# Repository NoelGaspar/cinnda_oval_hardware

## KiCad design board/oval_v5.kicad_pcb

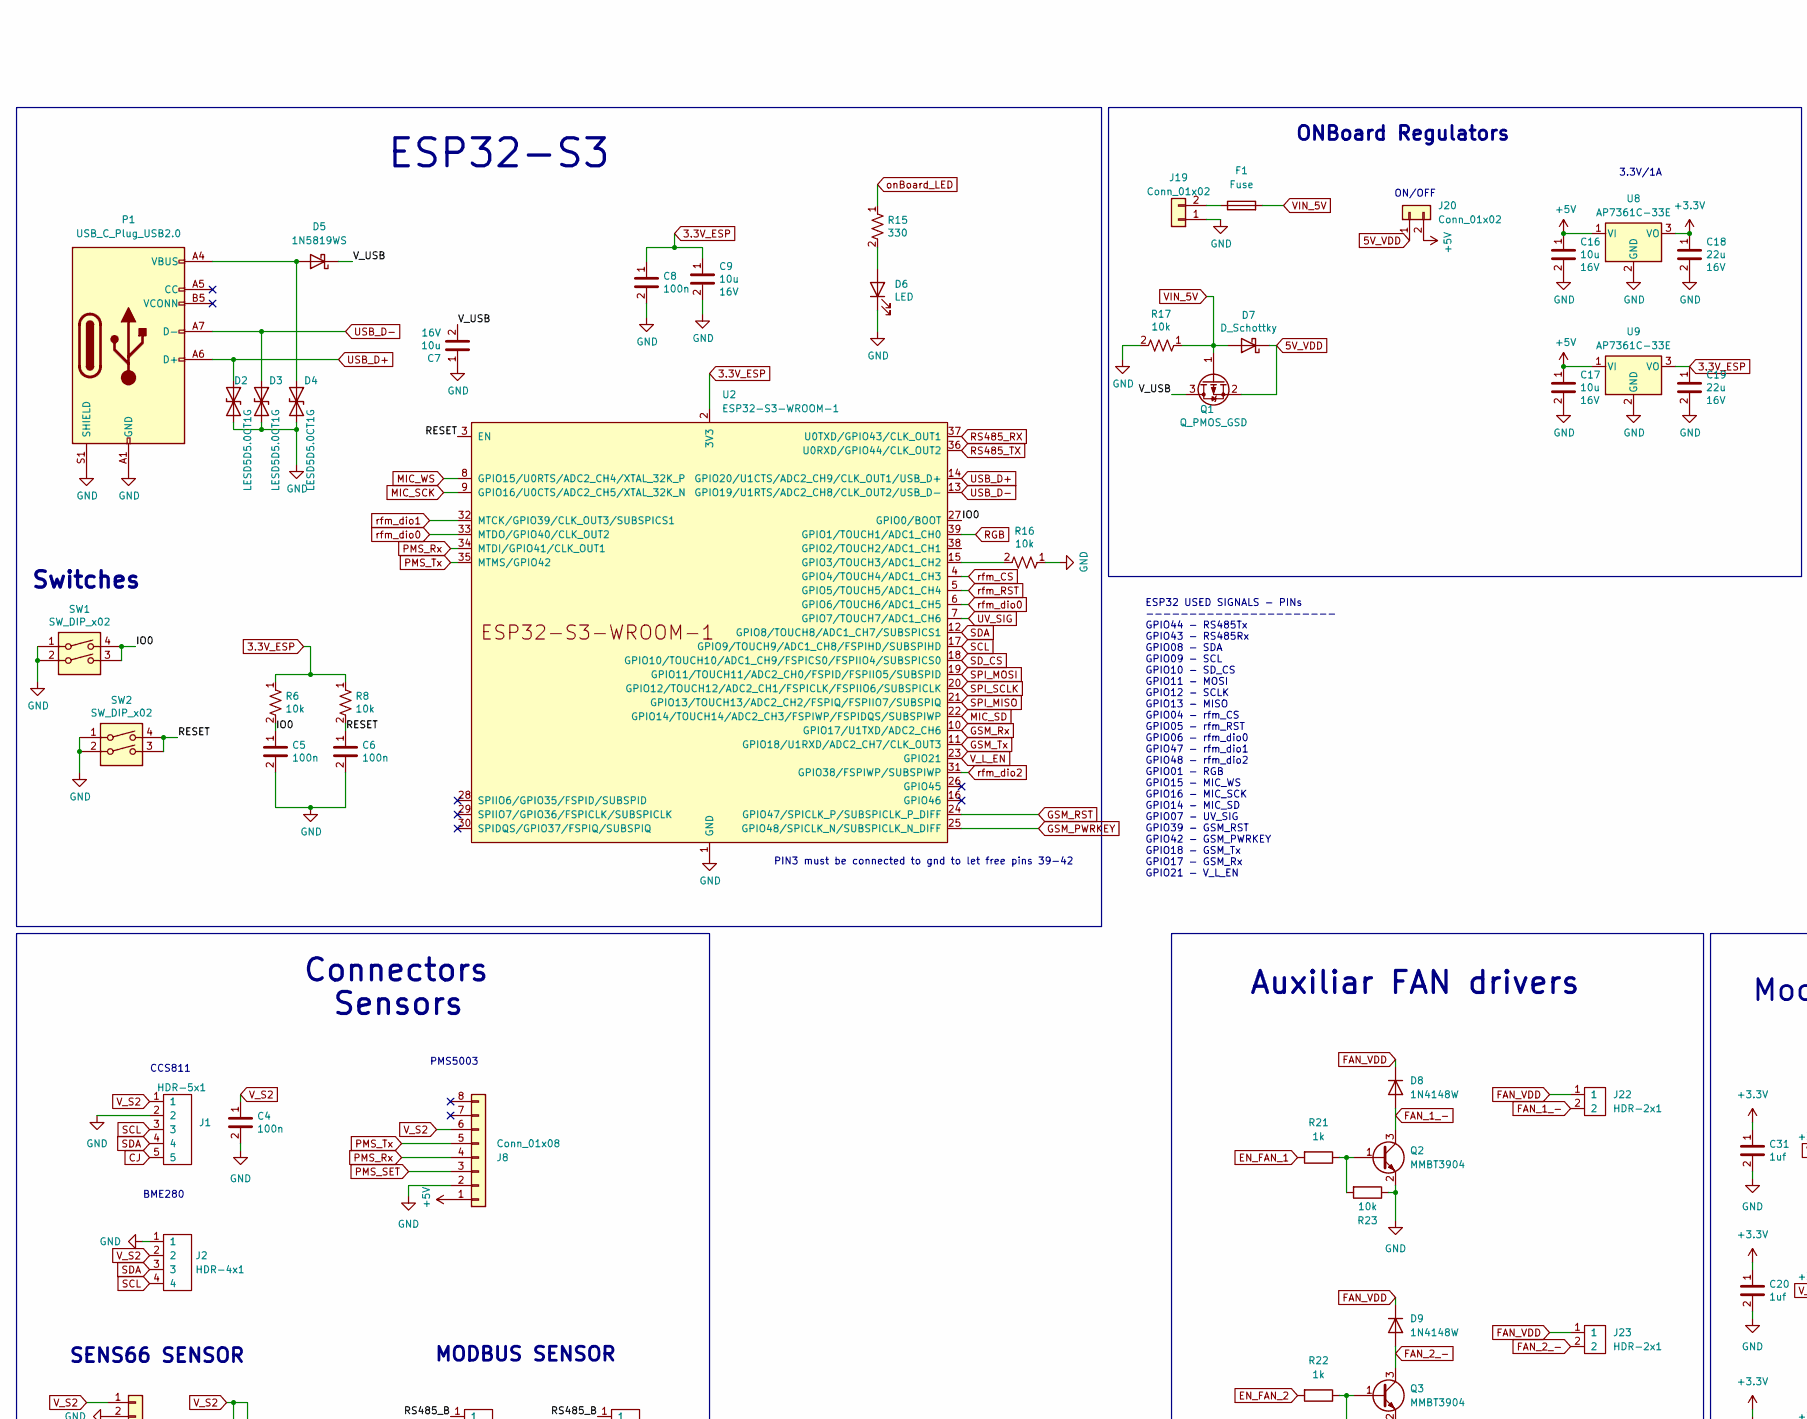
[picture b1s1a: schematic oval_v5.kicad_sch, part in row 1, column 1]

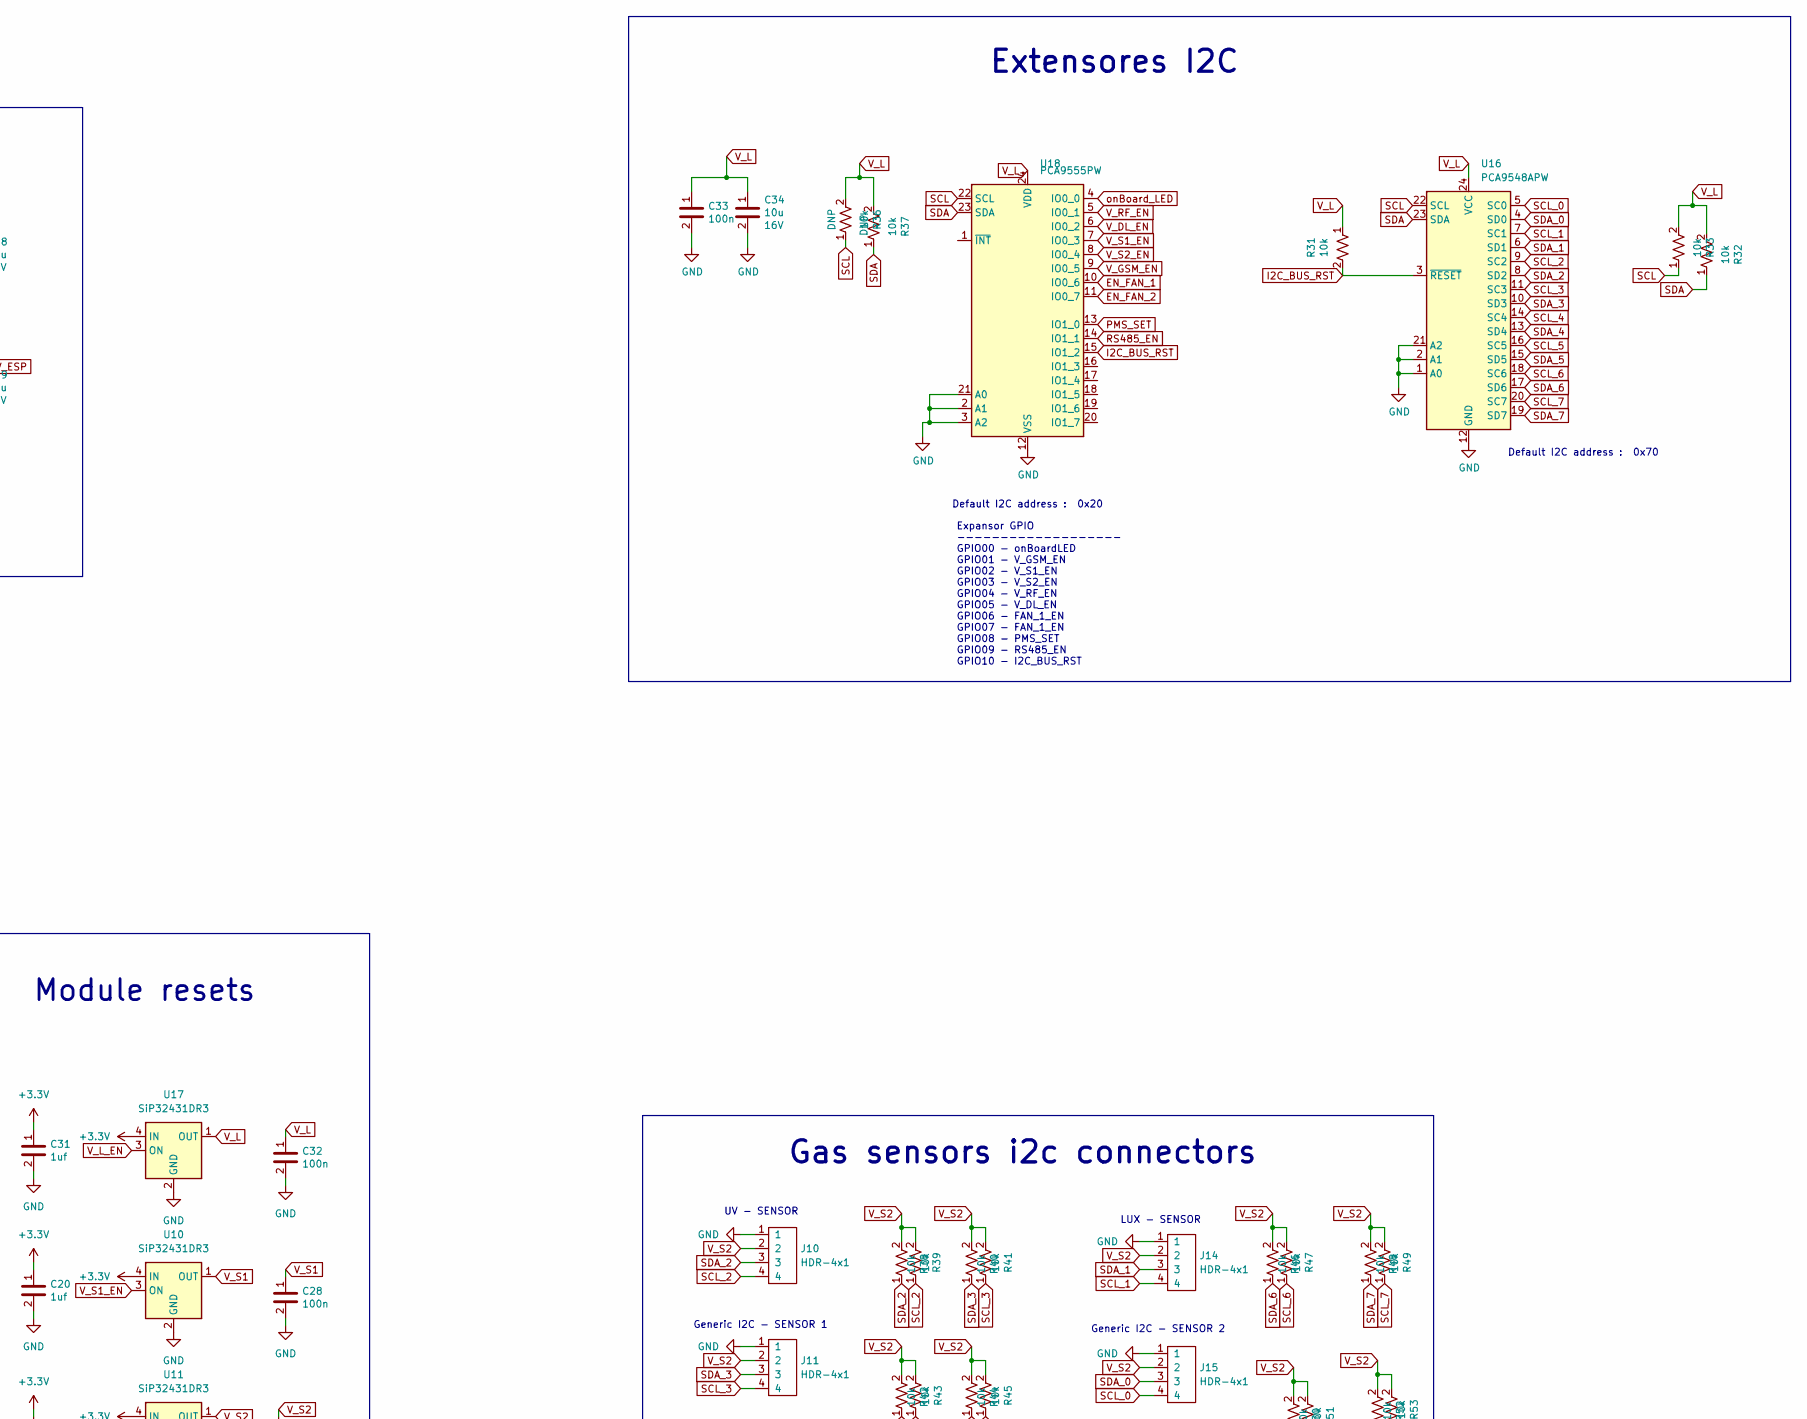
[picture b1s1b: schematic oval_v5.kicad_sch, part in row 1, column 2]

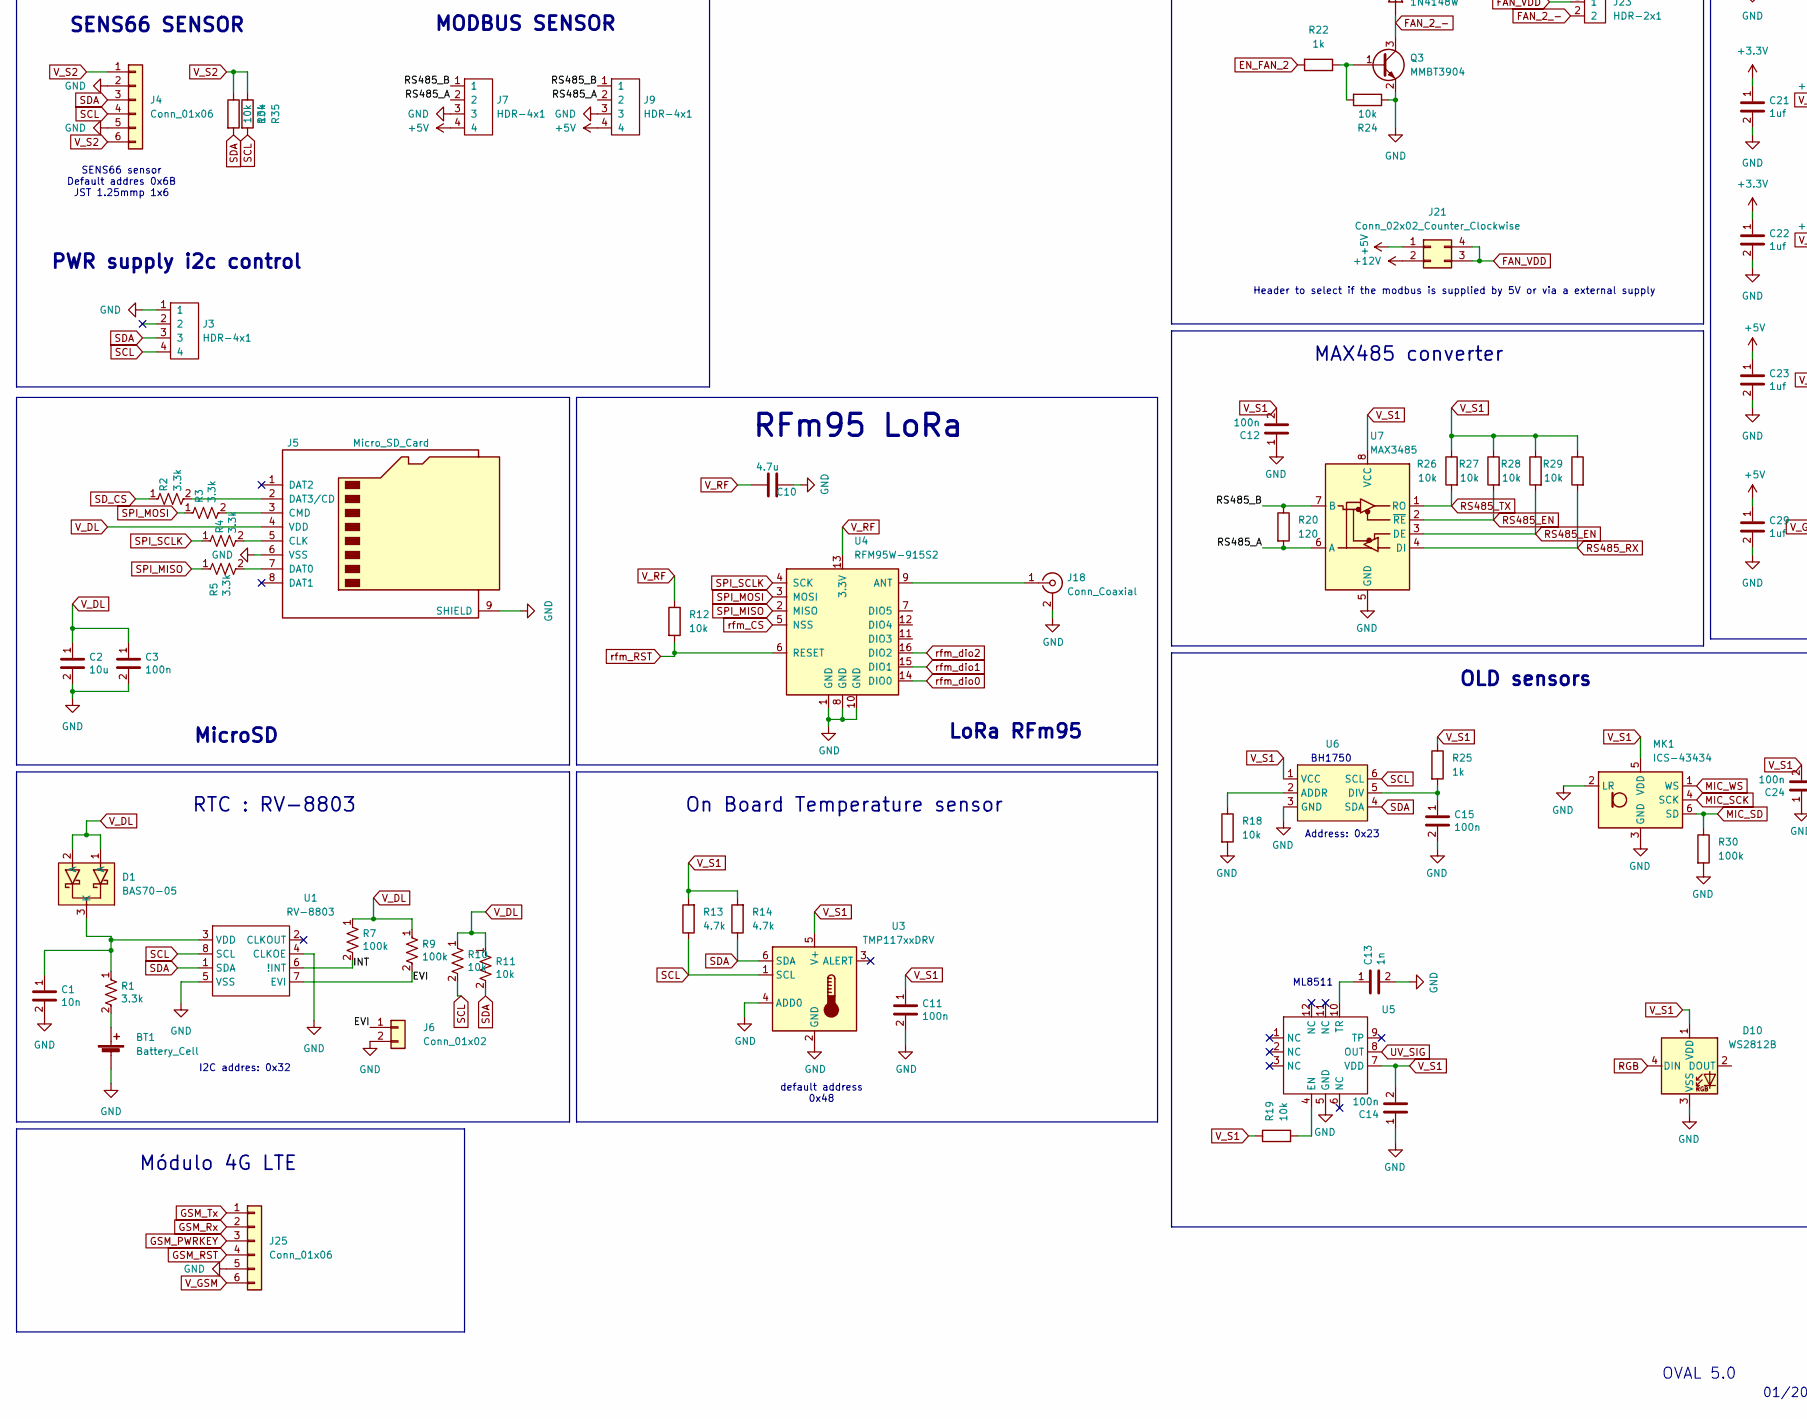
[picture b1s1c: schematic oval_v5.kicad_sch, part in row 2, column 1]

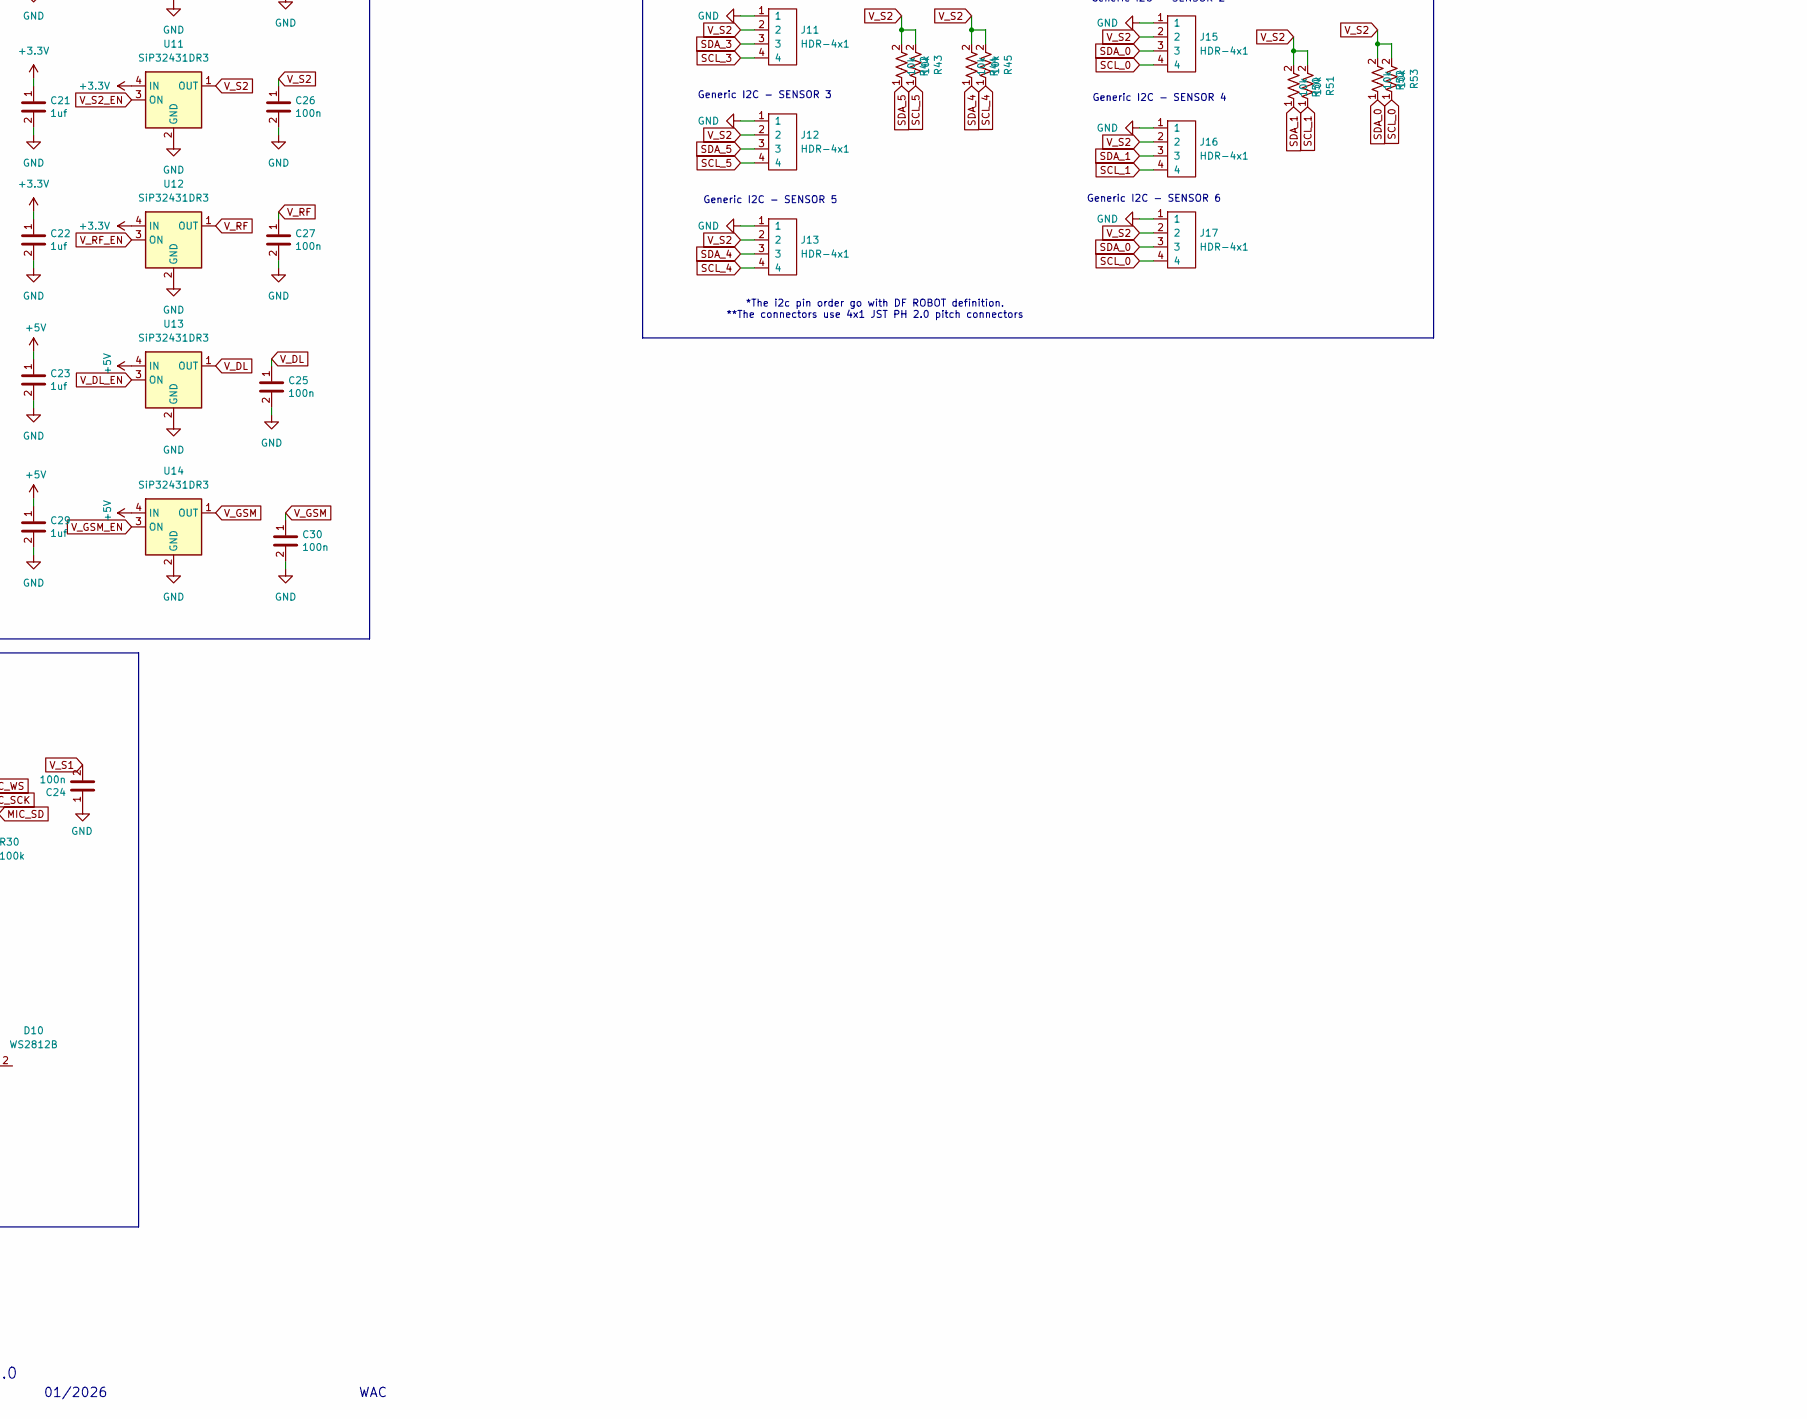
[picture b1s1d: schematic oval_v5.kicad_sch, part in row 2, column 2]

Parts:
BT1: Battery_Cell; BatteryHolder_Keystone_3000_1x12mm
C1: 10n; C_0603_1608Metric; Voltage rated 16V
C2, C7, C9, C16, C17, C34: 10u; C_0805_2012Metric; Voltage rated 16V
C3, C4, C5, C6, C8, C11, C12, C14, C15, C24, C25, C26, C27, C28, C30, C32, C33: 100n; C_0603_1608Metric; Voltage rated 16V
C10: 4.7u; C_0805_2012Metric
C13: 1n; C_0603_1608Metric; Voltage rated 16V
C18, C19: 22u; C_0805_2012Metric; Voltage rated 16V
C20, C21, C22, C23, C29, C31: 1uf; C_0805_2012Metric; Voltage rated 16V
D1: BAS70-05; SOT-23
D2, D3, D4: LESD5D5.0CT1G; D_SOD-523
D5: 1N5819WS; D_SOD-323_HandSoldering
D6: LED; LED_0603_1608Metric
D7: D_Schottky; D_SMA
D8, D9: 1N4148W; D_SOD-123
D10: WS2812B; LED_WS2812B_PLCC4_5.0x5.0mm_P3.2mm
F1: Fuse; Fuse_1206_3216Metric
J1: HDR-5x1; JST_PH_B5B-PH-K_1x05_P2.00mm_Vertical
J2, J3: HDR-4x1; JST_SH_SM04B-SRSS-TB_1x04-1MP_P1.00mm_Horizontal
J4: Conn_01x06; JST_GH_SM06B-GHS-TB_1x06-1MP_P1.25mm_Horizontal
J5: Micro_SD_Card; microSD_HC_Wuerth_693072010801
J6: Conn_01x02; SolderJumper-2_P1.3mm_Open_RoundedPad1.0x1.5mm
J7, J9, J10, J11, J12, J13, J14, J15, J16, J17: HDR-4x1; JST_PH_B4B-PH-K_1x04_P2.00mm_Vertical
J8: Conn_01x08; Molex_PicoBlade_53261-0871_1x08-1MP_P1.25mm_Horizontal
J18: Conn_Coaxial; U.FL_Molex_MCRF_73412-0110_Vertical
J19: Conn_01x02; Wago_734-132_1x02_P3.50mm_Vertical
J20: Conn_01x02; JST_PH_B2B-PH-K_1x02_P2.00mm_Vertical
J21: Conn_02x02_Counter_Clockwise; PinHeader_2x02_P2.54mm_Vertical
J22, J23: HDR-2x1; JST_PH_S2B-PH-SM4-TB_1x02-1MP_P2.00mm_Horizontal
J25: Conn_01x06; JST_PH_B6B-PH-K_1x06_P2.00mm_Vertical
MK1: ICS-43434; InvenSense_ICS-43434-6_3.5x2.65mm
P1: USB_C_Plug_USB2.0; USB_C_Receptacle_GCT_USB4105-xx-A_16P_TopMnt_Horizontal
Q1: Q_PMOS_GSD; SOT-23
Q2, Q3: MMBT3904; SOT-23
R1, R2, R3, R4, R5: 3.3k; R_0603_1608Metric
R6, R8, R10, R11, R12, R16, R17, R18, R19, R23, R24, R26, R27, R28, R29, R31, R32, R33, R34, R35, R36, R37, R38, R39, R40, R41, R42, R43, R44, R45, R46, R47, R48, R49, R50, R51, R52, R53: 10k; R_0603_1608Metric
R7, R9, R30: 100k; R_0603_1608Metric
R13, R14: 4.7k; R_0603_1608Metric
R15: 330; R_0603_1608Metric
R20: 120; R_0603_1608Metric
R21, R22, R25: 1k; R_0603_1608Metric
SW1, SW2: SW_DIP_x02; SMD_SWITCH
U1: RV-8803; SON-8
U2: ESP32-S3-WROOM-1
U3: TMP117xxDRV; WSON-6-1EP_2x2mm_P0.65mm_EP1x1.6mm
U4: RFM95W-915S2; HOPERF_RFM9XW_SMD
U5: C-TQFN12-4.0x3.7-1
U6: WSOF6I
U7: MAX3485; SOP-8_3.9x4.9mm_P1.27mm
U8, U9: AP7361C-33E; SOT-223-3_TabPin2
U10, U11, U12, U13, U14, U17: SiP32431DR3; SOT-363_SC-70-6
U16: PCA9548APW; TSSOP-24_4.4x7.8mm_P0.65mm
U18: PCA9555PW; TSSOP-24_4.4x7.8mm_P0.65mm

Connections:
3.3V_ESP: C8.1, C9.1, C19.1, R6.1, R8.1, U2.2 (3V3), U9.3 (VO)
5V_VDD: D7.1 (K), J20.1, Q1.2 (S)
+3.3V: C18.1, C20.1, C21.1, C22.1, C31.1, U8.3 (VO), U10.4 (IN), U11.4 (IN), U12.4 (IN), U17.4 (IN)
+5V: C16.1, C17.1, C23.1, C29.1, J7.4, J8.1, J9.4, J20.2, J21.1, U8.1 (VI), U9.1 (VI), U13.4 (IN), U14.4 (IN)
+12V: J21.2
/EVI: J6.1, R9.2, U1.7 (EVI)
/INT: R7.2, U1.6 (!INT)
/IO0: C5.1, R6.2, SW1.3, SW1.4, U2.27 (GPIO0/BOOT)
/RESET: C6.1, R8.2, SW2.3, SW2.4, U2.3 (EN)
/RS485_A: J7.2, J9.2, R20.2, U7.6 (A)
/RS485_B: J7.1, J9.1, R20.1, U7.7 (B)
/V_USB: C7.2, D5.1 (K), Q1.3 (D)
CJ: J1.5
EN_FAN_1: R21.2, U18.10 (IO0_6)
EN_FAN_2: R22.2, U18.11 (IO0_7)
FAN_1_-: D8.2 (A), J22.2, Q2.3 (C)
FAN_2_-: D9.2 (A), J23.2, Q3.3 (C)
FAN_VDD: D8.1 (K), D9.1 (K), J21.3, J21.4, J22.1, J23.1
GND: BT1.2 (-), C1.2, C2.2, C3.2, C4.2, C5.2, C6.2, C7.1, C8.2, C9.2, C10.1, C11.2, C12.1, C13.2, C14.1, C15.2, C16.2, C17.2, C18.2, C19.2, C20.2, C21.2, C22.2, C23.2, C24.1, C25.2, C26.2, C27.2, C28.2, C29.2, C30.2, C31.2, C32.2, C33.2, C34.2, D2.2 (A2), D3.2 (A2), D4.2 (A2), D6.1 (K), D10.3 (VSS), J1.2, J2.1, J3.1, J4.2, J4.5, J5.6 (VSS), J5.9 (SHIELD), J6.2, J7.3, J8.2, J9.3, J10.1, J11.1, J12.1, J13.1, J14.1, J15.1, J16.1, J17.1, J18.2 (Ext), J19.1, J25.5, MK1.2 (LR), MK1.3 (GND), P1.A1 (GND), P1.A12 (GND), P1.B1 (GND), P1.B12 (GND), P1.S1 (SHIELD), Q2.2 (E), Q3.2 (E), R16.1, R17.2, R18.2, R23.1, R24.1, R30.2, SW1.1, SW1.2, SW2.1, SW2.2, U1.4 (CLKOE), U1.5 (VSS), U2.1 (GND), U2.40 (GND), U2.41 (GND), U3.2 (GND), U3.4 (ADD0), U4.1 (GND), U4.8 (GND), U4.10 (GND), U5.5 (GND), U6.3 (GND), U7.5 (GND), U8.2 (GND), U9.2 (GND), U10.2 (GND), U10.5 (GND), U11.2 (GND), U11.5 (GND), U12.2 (GND), U12.5 (GND), U13.2 (GND), U13.5 (GND), U14.2 (GND), U14.5 (GND), U16.1 (A0), U16.2 (A1), U16.12 (GND), U16.21 (A2), U17.2 (GND), U17.5 (GND), U18.2 (A1), U18.3 (A2), U18.12 (VSS), U18.21 (A0)
GSM_PWRKEY: J25.3, U2.25 (GPIO48/SPICLK_N/SUBSPICLK_N_DIFF)
GSM_RST: J25.4, U2.24 (GPIO47/SPICLK_P/SUBSPICLK_P_DIFF)
GSM_Rx: J25.2, U2.10 (GPIO17/U1TXD/ADC2_CH6)
GSM_Tx: J25.1, U2.11 (GPIO18/U1RXD/ADC2_CH7/CLK_OUT3)
I2C_BUS_RST: R31.2, U16.3 (~RESET), U18.15 (IO1_2)
MIC_SCK: MK1.4 (SCK), U2.9 (GPIO16/U0CTS/ADC2_CH5/XTAL_32K_N)
MIC_SD: MK1.6 (SD), R30.1, U2.22 (GPIO14/TOUCH14/ADC2_CH3/FSPIWP/FSPIDQS/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)
MIC_WS: MK1.1 (WS), U2.8 (GPIO15/U0RTS/ADC2_CH4/XTAL_32K_P)
unnamed: BT1.1 (+), R1.2
unnamed: C1.1, D1.3 (K), R1.1, U1.3 (VDD)
unnamed: D4.1 (A1), D5.2 (A), P1.A4 (VBUS), P1.A9 (VBUS), P1.B4 (VBUS), P1.B9 (VBUS)
unnamed: D6.2 (A), R15.2
unnamed: J5.5 (CLK), R4.2
unnamed: J5.3 (CMD), R3.2
unnamed: J5.7 (DAT0), R5.2
unnamed: J5.2 (DAT3/CD), R2.2
unnamed: J18.1 (In), U4.9 (ANT)
unnamed: F1.1, J19.2
unnamed: Q2.1 (B), R21.1, R23.2
unnamed: Q3.1 (B), R22.1, R24.2
unnamed: R16.2, U2.15 (GPIO3/TOUCH3/ADC1_CH2)
unnamed: R19.2, U5.4 (EN)
unnamed: C13.1, U5.10 (TR)
unnamed: R18.1, U6.2 (ADDR)
unnamed: C15.1, R25.2, U6.5 (DIV)
PMS_Rx: J8.4, U2.34 (MTDI/GPIO41/CLK_OUT1)
PMS_SET: J8.3, U18.13 (IO1_0)
PMS_Tx: J8.5, U2.35 (MTMS/GPIO42)
RGB: D10.4 (DIN), U2.39 (GPIO1/TOUCH1/ADC1_CH0)
RS485_EN: R27.2, R28.2, U7.2 (~RE), U7.3 (DE), U18.14 (IO1_1)
RS485_RX: R29.2, U2.37 (U0TXD/GPIO43/CLK_OUT1), U7.4 (DI)
RS485_TX: R26.2, U2.36 (U0RXD/GPIO44/CLK_OUT2), U7.1 (RO)
SCL: J1.3, J2.4, J3.4, J4.4, R10.2, R13.1, R33.1, R35.2, R36.1, U1.8 (SCL), U2.17 (GPIO9/TOUCH9/ADC1_CH8/FSPIHD/SUBSPIHD), U3.1 (SCL), U6.6 (SCL), U16.22 (SCL), U18.22 (SCL)
SCL_0: J15.4, J17.4, R53.1, U16.5 (SC0)
SCL_1: J14.4, J16.4, R51.1, U16.7 (SC1)
SCL_2: J10.4, R39.1, U16.9 (SC2)
SCL_3: J11.4, R41.1, U16.11 (SC3)
SCL_4: J13.4, R45.1, U16.14 (SC4)
SCL_5: J12.4, R43.1, U16.16 (SC5)
SCL_6: R47.1, U16.18 (SC6)
SCL_7: R49.1, U16.20 (SC7)
SDA: J1.4, J2.3, J3.3, J4.3, R11.2, R14.1, R32.1, R34.2, R37.1, U1.1 (SDA), U2.12 (GPIO8/TOUCH8/ADC1_CH7/SUBSPICS1), U3.6 (SDA), U6.4 (SDA), U16.23 (SDA), U18.23 (SDA)
SDA_0: J15.3, J17.3, R52.1, U16.4 (SD0)
SDA_1: J14.3, J16.3, R50.1, U16.6 (SD1)
SDA_2: J10.3, R38.1, U16.8 (SD2)
SDA_3: J11.3, R40.1, U16.10 (SD3)
SDA_4: J13.3, R44.1, U16.13 (SD4)
SDA_5: J12.3, R42.1, U16.15 (SD5)
SDA_6: R46.1, U16.17 (SD6)
SDA_7: R48.1, U16.19 (SD7)
SD_CS: R2.1, U2.18 (GPIO10/TOUCH10/ADC1_CH9/FSPICS0/FSPIIO4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)
SPI_MISO: R5.1, U2.21 (GPIO13/TOUCH13/ADC2_CH2/FSPIQ/FSPIIO7/S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), U4.2 (MISO)
SPI_MOSI: R3.1, U2.19 (GPIO11/TOUCH11/ADC2_CH0/FSPID/FSPIIO5/S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), U4.3 (MOSI)
SPI_SCLK: R4.1, U2.20 (GPIO12/TOUCH12/ADC2_CH1/FSPICLK/FSPIIO6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), U4.4 (SCK)
USB_D+: D2.1 (A1), P1.A6 (D+), U2.14 (GPIO20/U1CTS/ADC2_CH9/CLK_OUT1/USB_D+)
USB_D-: D3.1 (A1), P1.A7 (D-), U2.13 (GPIO19/U1RTS/ADC2_CH8/CLK_OUT2/USB_D-)
UV_SIG: U2.7 (GPIO7/TOUCH7/ADC1_CH6), U5.8 (OUT)
VIN_5V: D7.2 (A), F1.2, Q1.1 (G), R17.1
V_DL: C2.1, C3.1, C25.1, D1.1 (A), D1.2 (A), J5.4 (VDD), R7.1, R9.1, R10.1, R11.1, U13.1 (OUT)
V_DL_EN: U13.3 (ON), U18.6 (IO0_2)
V_GSM: C30.1, J25.6, U14.1 (OUT)
V_GSM_EN: U14.3 (ON), U18.9 (IO0_5)
V_L: C32.1, C33.1, C34.1, R31.1, R32.2, R33.2, R36.2, R37.2, U16.24 (VCC), U17.1 (OUT), U18.24 (VDD)
V_L_EN: U2.23 (GPIO21), U17.3 (ON)
V_RF: C10.2, C27.1, R12.1, U4.13 (3.3V), U12.1 (OUT)
V_RF_EN: U12.3 (ON), U18.5 (IO0_1)
V_S1: C11.1, C12.2, C14.2, C24.2, C28.1, D10.1 (VDD), MK1.5 (VDD), R13.2, R14.2, R19.1, R25.1, R26.1, R27.1, R28.1, R29.1, U3.5 (V+), U5.7 (VDD), U6.1 (VCC), U7.8 (VCC), U10.1 (OUT)
V_S1_EN: U10.3 (ON), U18.7 (IO0_3)
V_S2: C4.1, C26.1, J1.1, J2.2, J4.1, J4.6, J8.6, J10.2, J11.2, J12.2, J13.2, J14.2, J15.2, J16.2, J17.2, R34.1, R35.1, R38.2, R39.2, R40.2, R41.2, R42.2, R43.2, R44.2, R45.2, R46.2, R47.2, R48.2, R49.2, R50.2, R51.2, R52.2, R53.2, U11.1 (OUT)
V_S2_EN: U11.3 (ON), U18.8 (IO0_4)
onBoard_LED: R15.1, U18.4 (IO0_0)
rfm_CS: U2.4 (GPIO4/TOUCH4/ADC1_CH3), U4.5 (NSS)
rfm_RST: R12.2, U2.5 (GPIO5/TOUCH5/ADC1_CH4), U4.6 (RESET)
rfm_dio0: U2.6 (GPIO6/TOUCH6/ADC1_CH5), U2.33 (MTDO/GPIO40/CLK_OUT2), U4.14 (DIO0)
rfm_dio1: U2.32 (MTCK/GPIO39/CLK_OUT3/SUBSPICS1), U4.15 (DIO1)
rfm_dio2: U2.31 (GPIO38/FSPIWP/SUBSPIWP), U4.16 (DIO2)

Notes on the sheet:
Address: 0x23
Header to select if the modbus is supplied by 5V or via a external supply
Generic I2C - SENSOR 6
ESP32 USED SIGNALS - PINs ---------------------- GPIO44 - RS485Tx GPIO43 - RS485Rx GPIO08 - SDA GPIO09 - SCL GPIO10 - SD_CS GPIO11 - MOSI GPIO12 - SCLK GPIO13 - MISO GPIO04 - rfm_CS GPIO05 - rfm_RST GPIO06 - rfm_dio0 GPIO47 - rfm_dio1 GPIO48 - rfm_dio2 GPIO01 - RGB GPIO15 - MIC_WS GPIO16 - MIC_SCK 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
Generic I2C - SENSOR 1
On Board Temperature sensor
ESP32-S3
UV - SENSOR
MODBUS SENSOR
PWR supply i2c control
MicroSD
Generic I2C - SENSOR 4
ON/OFF
Generic I2C - SENSOR 5
WAC
Module resets
Generic I2C - SENSOR 2
PMS5003
Switches
OVAL 5.0
ONBoard Regulators
Expansor GPIO ------------------- GPIO00 - onBoardLED GPIO01 - V_GSM_EN GPIO02 - V_S1_EN GPIO03 - V_S2_EN GPIO04 - V_RF_EN GPIO05 - V_DL_EN GPIO06 - FAN_1_EN GPIO07 - FAN_1_EN GPIO08 - PMS_SET GPIO09 - RS485_EN GPIO10 - I2C_BUS_RST
SENS66 SENSOR
BH1750
OLD sensors
01/2026
LoRa RFm95
Sensors
*The i2c pin order go with DF ROBOT definition. **The connectors use 4x1 JST PH 2.0 pitch connectors
LUX - SENSOR
Gas sensors i2c connectors
ML8511
Default I2C address : 0x20
SENS66 sensor Default addres 0x6B JST 1.25mmp 1x6
PIN3 must be connected to gnd to let free pins 39-42
Generic I2C - SENSOR 3
Connectors
BME280
Default I2C address : 0x70
RTC : RV-8803

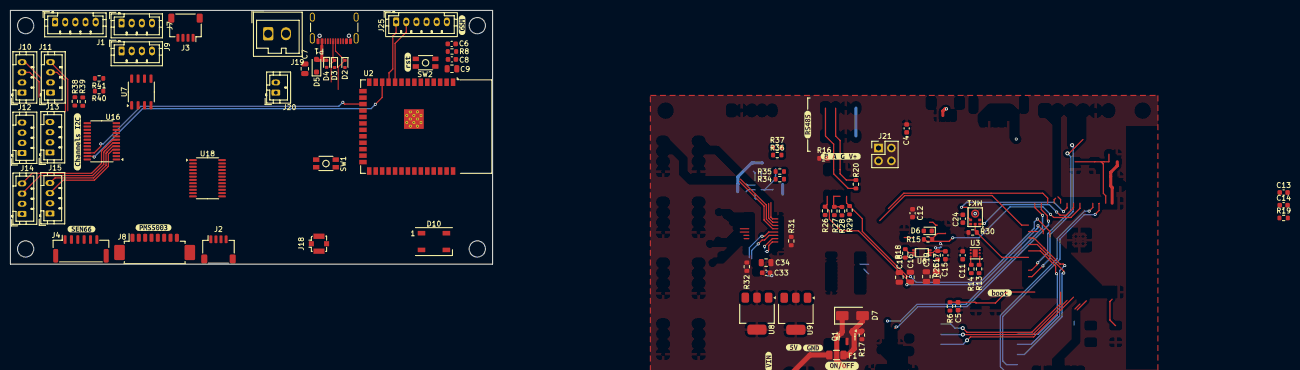
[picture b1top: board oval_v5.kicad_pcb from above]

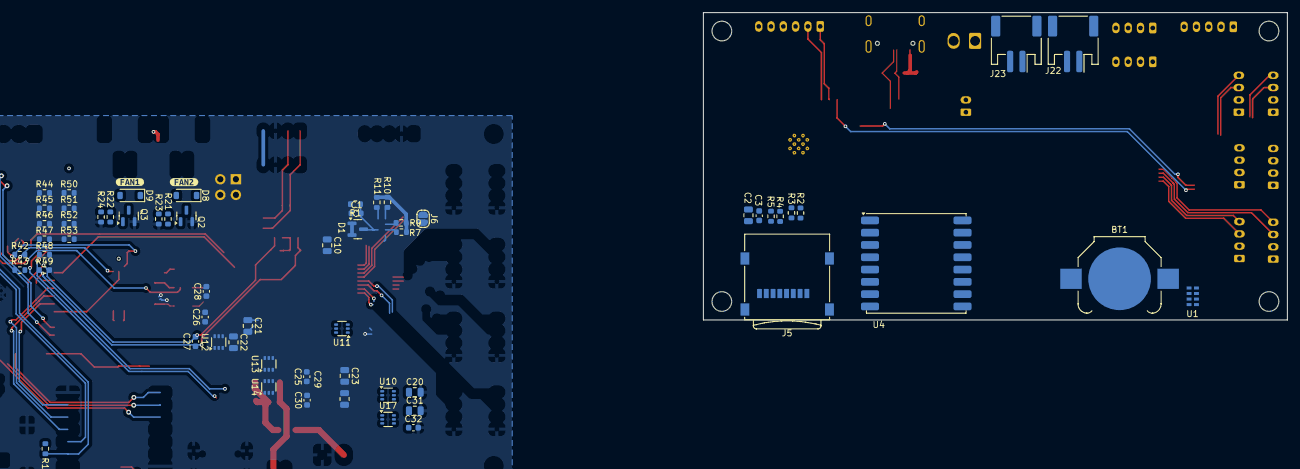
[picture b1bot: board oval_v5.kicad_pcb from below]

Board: 4 copper layers, 95.0 x 50.0 mm, 157 parts (62 on the bottom side), 90 nets.

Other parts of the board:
kibuzzard-69A867E5: G***; kibuzzard-69A867E5
kibuzzard-69A86736: G***; kibuzzard-69A86736
kibuzzard-69B0484A: G***; kibuzzard-69B0484A
kibuzzard-69B0485B: G***; kibuzzard-69B0485B
kibuzzard-69B0486A: G***; kibuzzard-69B0486A
kibuzzard-69B04879: G***; kibuzzard-69B04879
kibuzzard-699C8DA6: G***; kibuzzard-699C8DA6
kibuzzard-699C8DCD: G***; kibuzzard-699C8DCD
kibuzzard-6994EF08: G***; kibuzzard-6994EF08
kibuzzard-6994F00B: G***; kibuzzard-6994F00B
kibuzzard-6994F01D: G***; kibuzzard-6994F01D
kibuzzard-6994F21E: G***; kibuzzard-6994F21E
kibuzzard-69934830: G***; kibuzzard-69934830
kibuzzard-69934843: G***; kibuzzard-69934843

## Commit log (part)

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2026-02-02 working on schematic, main componentes defined
2026-02-12 starting layout
2026-02-13 commponent placement finished
2026-02-20 minor changes
2026-02-23 working on layout - defining connectors and cables
2026-02-25 assignint pines
2026-03-02 updateing 27/02
2026-03-04 adding layout review
2026-03-09 routing pads
2026-03-10 i2c multiplexer routed
2026-03-11 i2c adding pull up resistors
2026-03-13 adding work in layout
2026-03-18 bom ready
2026-03-24 working on bom
2026-03-25 bom already finished
2026-03-26 cart finished and upload to the provider
